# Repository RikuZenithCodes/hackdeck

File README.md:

# Hackdeck
Hackdeck is my personal take on a Steam Deck inspired hackpad a compact, all in one macro controller built for both utility and style. It features 6 programmable mechanical keys used for launching applications (such as discord, spotify, twitch, etc), a rotary encoder for volume or scroll control, and a crisp OLED display to show real-time feedback like current track info, system stats, or custom menus.
# Schematic and PCB

# Components
1x XIAO RP2040<br/>
6x Cherry MX Switches<br/>
6x Keycaps<br/>
1x EC11 Rotary Encoder<br/>
1x .91" OLED Display<br/>
4x SK6812 MINI Leds<br/>
Custom 3D Printed Top Case<br/>
Custom 3D Printed Bottom Case<br/>

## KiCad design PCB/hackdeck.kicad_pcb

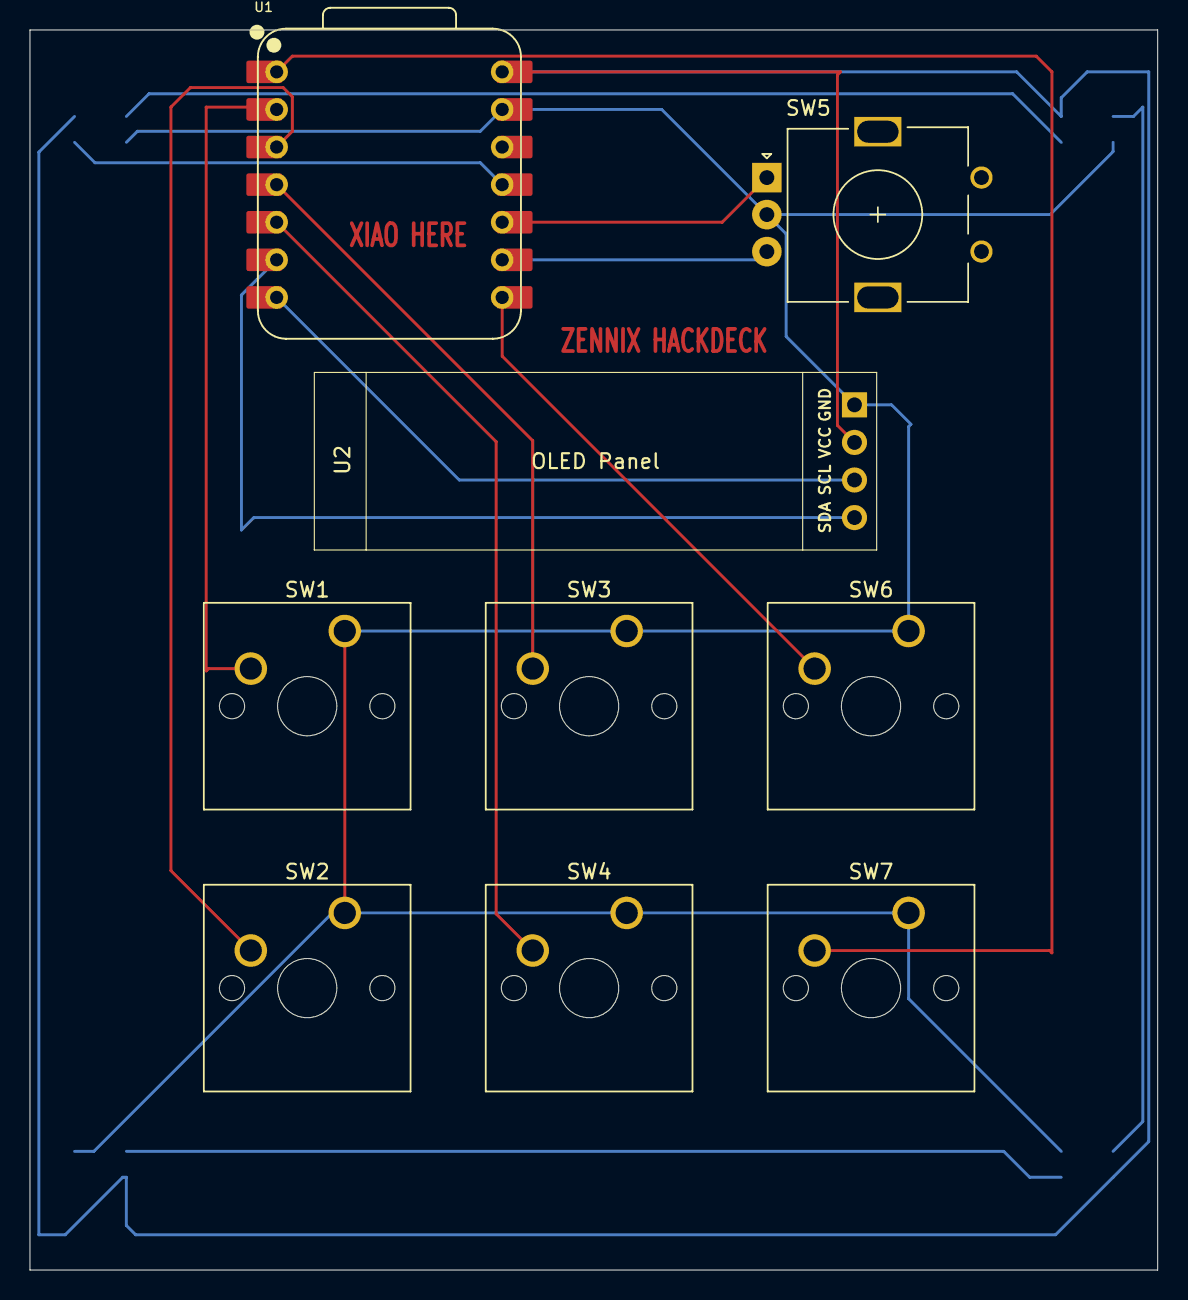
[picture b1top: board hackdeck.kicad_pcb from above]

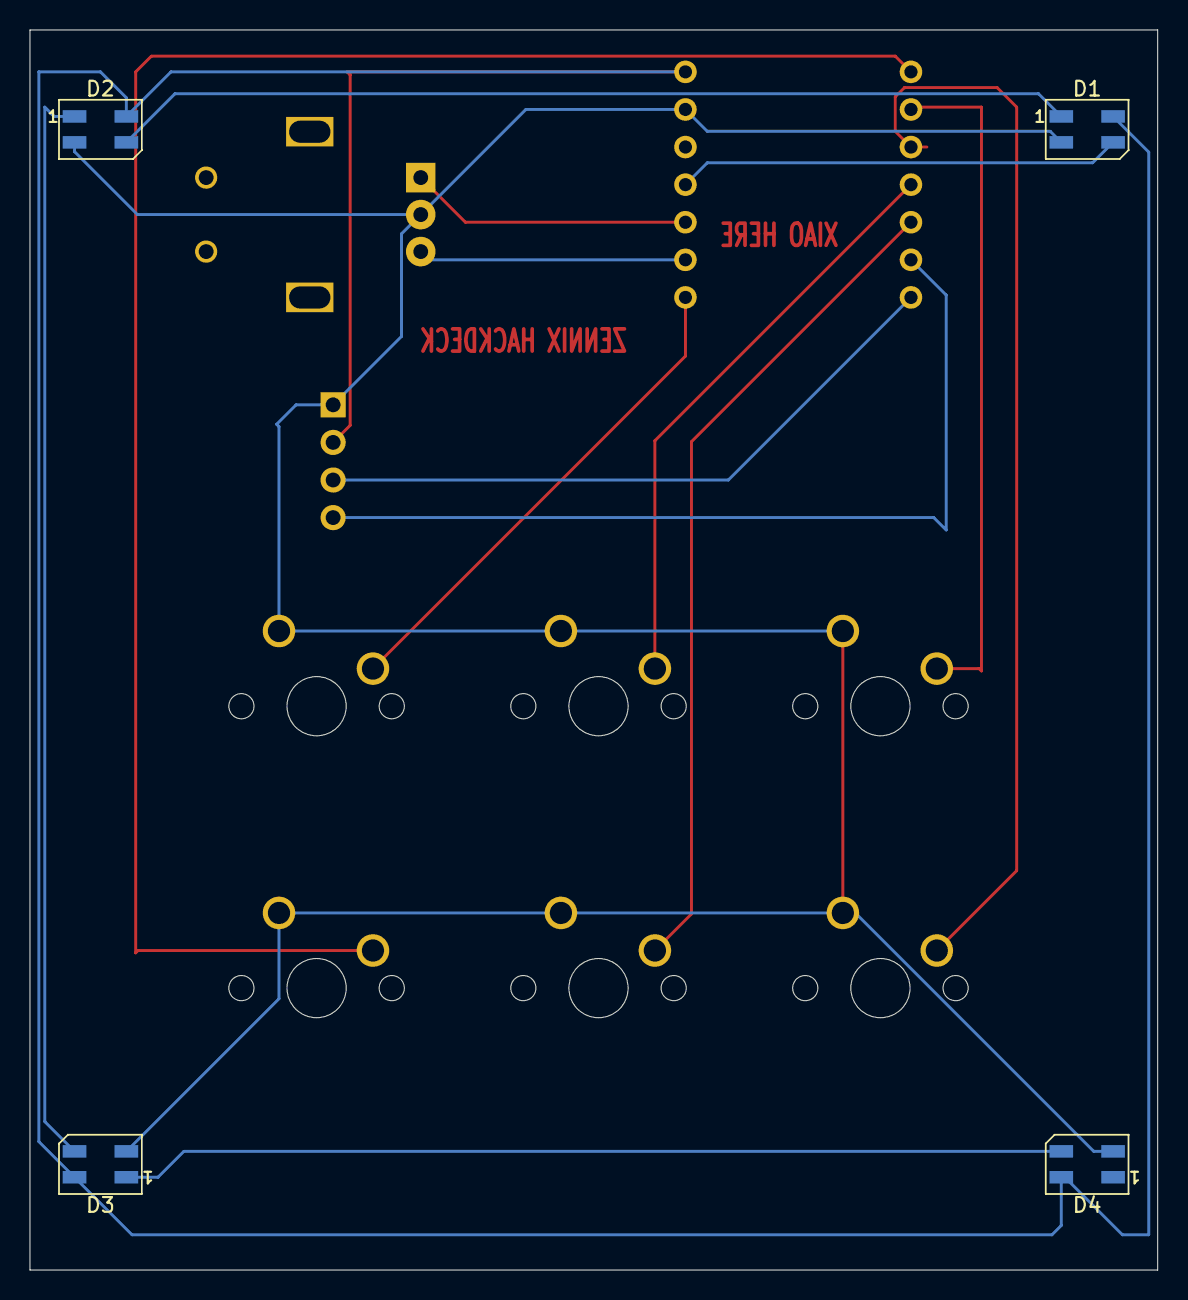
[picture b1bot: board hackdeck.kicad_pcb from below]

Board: 2 copper layers, 76.2 x 83.8 mm, 13 parts (4 on the bottom side), 16 nets.

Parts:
D1, D2, D3, D4: SK6812MINI; LED_SK6812MINI_PLCC4_3.5x3.5mm_P1.75mm
SW1, SW2, SW3, SW4, SW6, SW7: SW_Push; SW_Cherry_MX_1.00u_PCB
SW5: RotaryEncoder; RotaryEncoder_Alps_EC11E_Vertical_H20mm
U1: XIAO-RP2040-DIP
U2: OLED; SSD1306-0.91-OLED-4pin-128x32

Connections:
+5V: D1.4 (VDD), D2.4 (VDD), D3.4 (VDD), D4.4 (VDD), U1.14 (VBUS), U2.2 (VCC)
GND: D1.2 (VSS), D2.2 (VSS), D3.2 (VSS), D4.2 (VSS), SW1.1, SW2.1, SW3.1, SW4.1, SW5.C, SW6.1, SW7.1, U1.13 (GND), U2.1 (GND)
unnamed: D1.3 (DIN), U1.11 (GPIO3/MOSI)
unnamed: D1.1 (DOUT), D2.3 (DIN)
unnamed: D2.1 (DOUT), D3.3 (DIN)
unnamed: D3.1 (DOUT), D4.3 (DIN)
unnamed: U1.7 (GPIO0/TX), U2.3 (SCL)
unnamed: SW6.2, U1.8 (GPIO1/RX)
unnamed: SW5.B, U1.9 (GPIO2/SCK)
unnamed: SW5.A, U1.10 (GPIO4/MISO)
unnamed: SW4.2, U1.5 (GPIO6/SDA)
unnamed: U1.6 (GPIO7/SCL), U2.4 (SDA)
unnamed: SW7.2, U1.1 (GPIO26/ADC0/A0)
unnamed: SW1.2, U1.2 (GPIO27/ADC1/A1)
unnamed: SW2.2, U1.3 (GPIO28/ADC2/A2)
unnamed: SW3.2, U1.4 (GPIO29/ADC3/A3)

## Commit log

2025-06-29 init
2025-06-29 final stretch
2025-06-29 OLED and Rotary fix
